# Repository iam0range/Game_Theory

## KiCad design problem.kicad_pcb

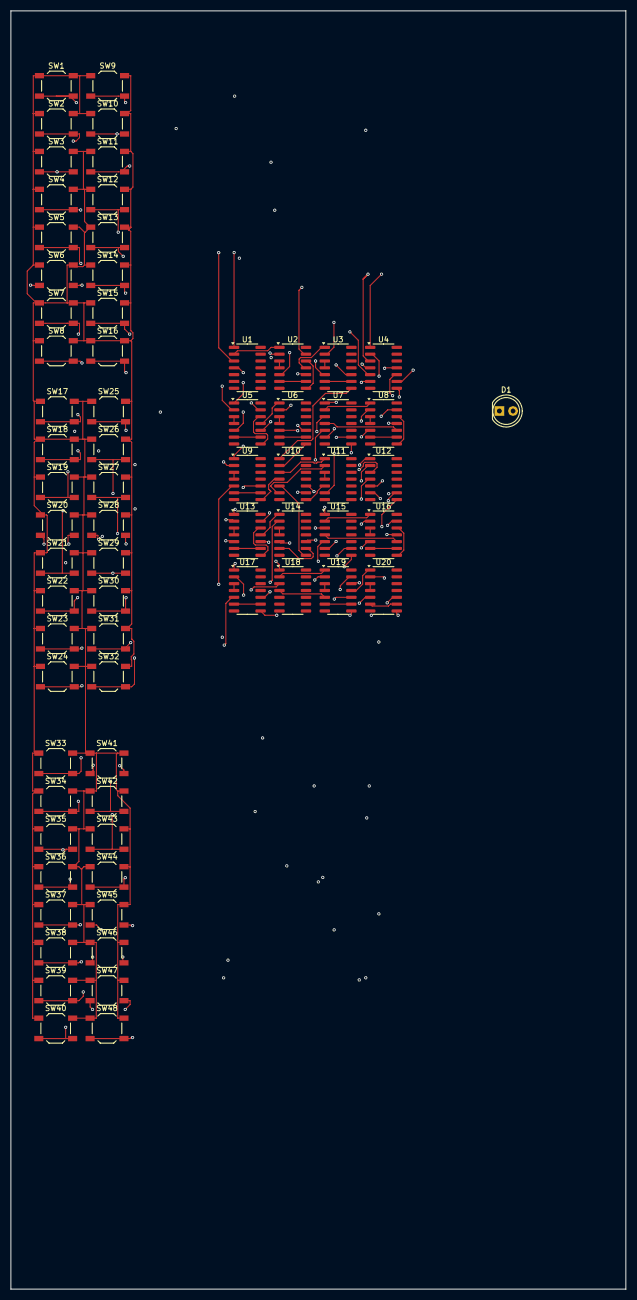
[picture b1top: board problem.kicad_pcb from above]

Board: 4 copper layers, 114.5 x 238.0 mm, 69 parts (0 on the bottom side), 117 nets.

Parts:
D1: LED; LED_D5.0mm
SW1, SW2, SW3, SW4, SW5, SW6, SW7, SW8, SW9, SW10, SW11, SW12, SW13, SW14, SW15, SW16, SW17, SW18, SW19, SW20, SW21, SW22, SW23, SW24, SW25, SW26, SW27, SW28, SW29, SW30, SW31, SW32, SW33, SW34, SW35, SW36, SW37, SW38, SW39, SW40, SW41, SW42, SW43, SW44, SW45, SW46, SW47, SW48: SW_SPST; SW_SPST_TL3342
U1, U4, U7, U12, U15, U18: 74AHC04; SOIC-14_3.9x8.7mm_P1.27mm
U2, U3, U5, U6, U8, U9, U10, U11, U13, U14, U16, U17, U19, U20: 74LS08; SOIC-14_3.9x8.7mm_P1.27mm

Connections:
+3.3V: SW1.1 (A), SW2.1 (A), SW3.1 (A), SW4.1 (A), SW5.1 (A), SW6.1 (A), SW7.1 (A), SW8.1 (A), SW9.1 (A), SW10.1 (A), SW11.1 (A), SW12.1 (A), SW13.1 (A), SW14.1 (A), SW15.1 (A), SW16.1 (A), SW17.1 (A), SW18.1 (A), SW19.1 (A), SW20.1 (A), SW21.1 (A), SW22.1 (A), SW23.1 (A), SW24.1 (A), SW25.1 (A), SW26.1 (A), SW27.1 (A), SW28.1 (A), SW29.1 (A), SW30.1 (A), SW31.1 (A), SW32.1 (A), SW33.1 (A), SW34.1 (A), SW35.1 (A), SW36.1 (A), SW37.1 (A), SW38.1 (A), SW39.1 (A), SW40.1 (A), SW41.1 (A), SW42.1 (A), SW43.1 (A), SW44.1 (A), SW45.1 (A), SW46.1 (A), SW47.1 (A), SW48.1 (A)
unnamed: D1.1 (K), U11.6
unnamed: SW1.2 (B), U1.1
unnamed: SW2.2 (B), U2.2
unnamed: SW3.2 (B), U2.5
unnamed: SW4.2 (B), U1.3
unnamed: SW5.2 (B), U2.13
unnamed: SW6.2 (B), U3.2
unnamed: SW7.2 (B), U3.5
unnamed: SW8.2 (B), U3.10
unnamed: SW9.2 (B), U4.1
unnamed: SW10.2 (B), U5.2
unnamed: SW11.2 (B), U5.5
unnamed: SW12.2 (B), U4.3
unnamed: SW13.2 (B), U5.13
unnamed: SW14.2 (B), U4.5
unnamed: SW15.2 (B), U4.9
unnamed: SW16.2 (B), U4.11
unnamed: SW17.2 (B), U7.1
unnamed: SW18.2 (B), U8.2
unnamed: SW19.2 (B), U8.5
unnamed: SW20.2 (B), U7.3
unnamed: SW21.2 (B), U7.5
unnamed: SW22.2 (B), U7.9
unnamed: SW23.2 (B), U9.5
unnamed: SW24.2 (B), U9.10
unnamed: SW25.2 (B), U12.1
unnamed: SW26.2 (B), U13.2
unnamed: SW27.2 (B), U13.5
unnamed: SW28.2 (B), U13.10
unnamed: SW29.2 (B), U12.3
unnamed: SW30.2 (B), U14.2
unnamed: SW31.2 (B), U12.5
unnamed: SW32.2 (B), U12.9
unnamed: SW33.2 (B), U15.1
unnamed: SW34.2 (B), U16.2
unnamed: SW35.2 (B), U16.5
unnamed: SW36.2 (B), U15.3
unnamed: SW37.2 (B), U15.5
unnamed: SW38.2 (B), U17.2
unnamed: SW39.2 (B), U17.5
unnamed: SW40.2 (B), U15.9
unnamed: SW41.2 (B), U18.1
unnamed: SW42.2 (B), U19.2
unnamed: SW43.2 (B), U18.3
unnamed: SW44.2 (B), U19.10
unnamed: SW45.2 (B), U19.13
unnamed: SW46.2 (B), U20.2
unnamed: SW47.2 (B), U20.5
unnamed: SW48.2 (B), U20.10
unnamed: U1.2, U2.1
unnamed: U1.4, U2.10
unnamed: U2.3, U2.4
unnamed: U2.6, U2.9
unnamed: U2.11, U3.1
unnamed: U2.8, U2.12
unnamed: U3.3, U3.4
unnamed: U3.6, U3.9
unnamed: U4.2, U5.1
unnamed: U4.4, U5.10
unnamed: U4.6, U6.2
unnamed: U4.8, U6.5
unnamed: U4.10, U6.10
unnamed: U5.3, U5.4
unnamed: U5.6, U5.9
unnamed: U5.11, U6.1
unnamed: U5.8, U5.12
unnamed: U6.3, U6.4
unnamed: U6.6, U6.9
unnamed: U7.2, U8.1
unnamed: U7.4, U8.10
unnamed: U7.6, U8.13
unnamed: U7.8, U9.2
unnamed: U8.3, U8.4
unnamed: U8.6, U8.9
unnamed: U8.11, U9.1
unnamed: U8.8, U8.12
unnamed: U9.3, U9.4
unnamed: U9.6, U9.9
unnamed: U3.8, U10.1
unnamed: U6.8, U10.2
unnamed: U10.3, U11.1
unnamed: U9.8, U10.4
unnamed: U10.5, U14.8
unnamed: U10.6, U11.2
unnamed: U10.8, U11.5
unnamed: U10.9, U17.8
unnamed: U10.10, U20.8
unnamed: U11.3, U11.4
unnamed: U12.2, U13.1
unnamed: U12.4, U13.13
unnamed: U12.6, U14.5
unnamed: U12.8, U14.10
unnamed: U13.3, U13.4
unnamed: U13.6, U13.9
unnamed: U13.11, U14.1
unnamed: U13.8, U13.12
unnamed: U14.3, U14.4
unnamed: U14.6, U14.9
unnamed: U15.2, U16.1
unnamed: U15.4, U16.10
unnamed: U15.6, U16.13
unnamed: U15.8, U17.10
unnamed: U16.3, U16.4
unnamed: U16.6, U16.9
unnamed: U16.11, U17.1
unnamed: U16.8, U16.12
unnamed: U17.3, U17.4
unnamed: U17.6, U17.9
unnamed: U18.2, U19.1
unnamed: U18.4, U19.5
unnamed: U19.3, U19.4
unnamed: U19.6, U19.9
unnamed: U19.11, U20.1
unnamed: U19.8, U19.12
unnamed: U20.3, U20.4
unnamed: U20.6, U20.9
